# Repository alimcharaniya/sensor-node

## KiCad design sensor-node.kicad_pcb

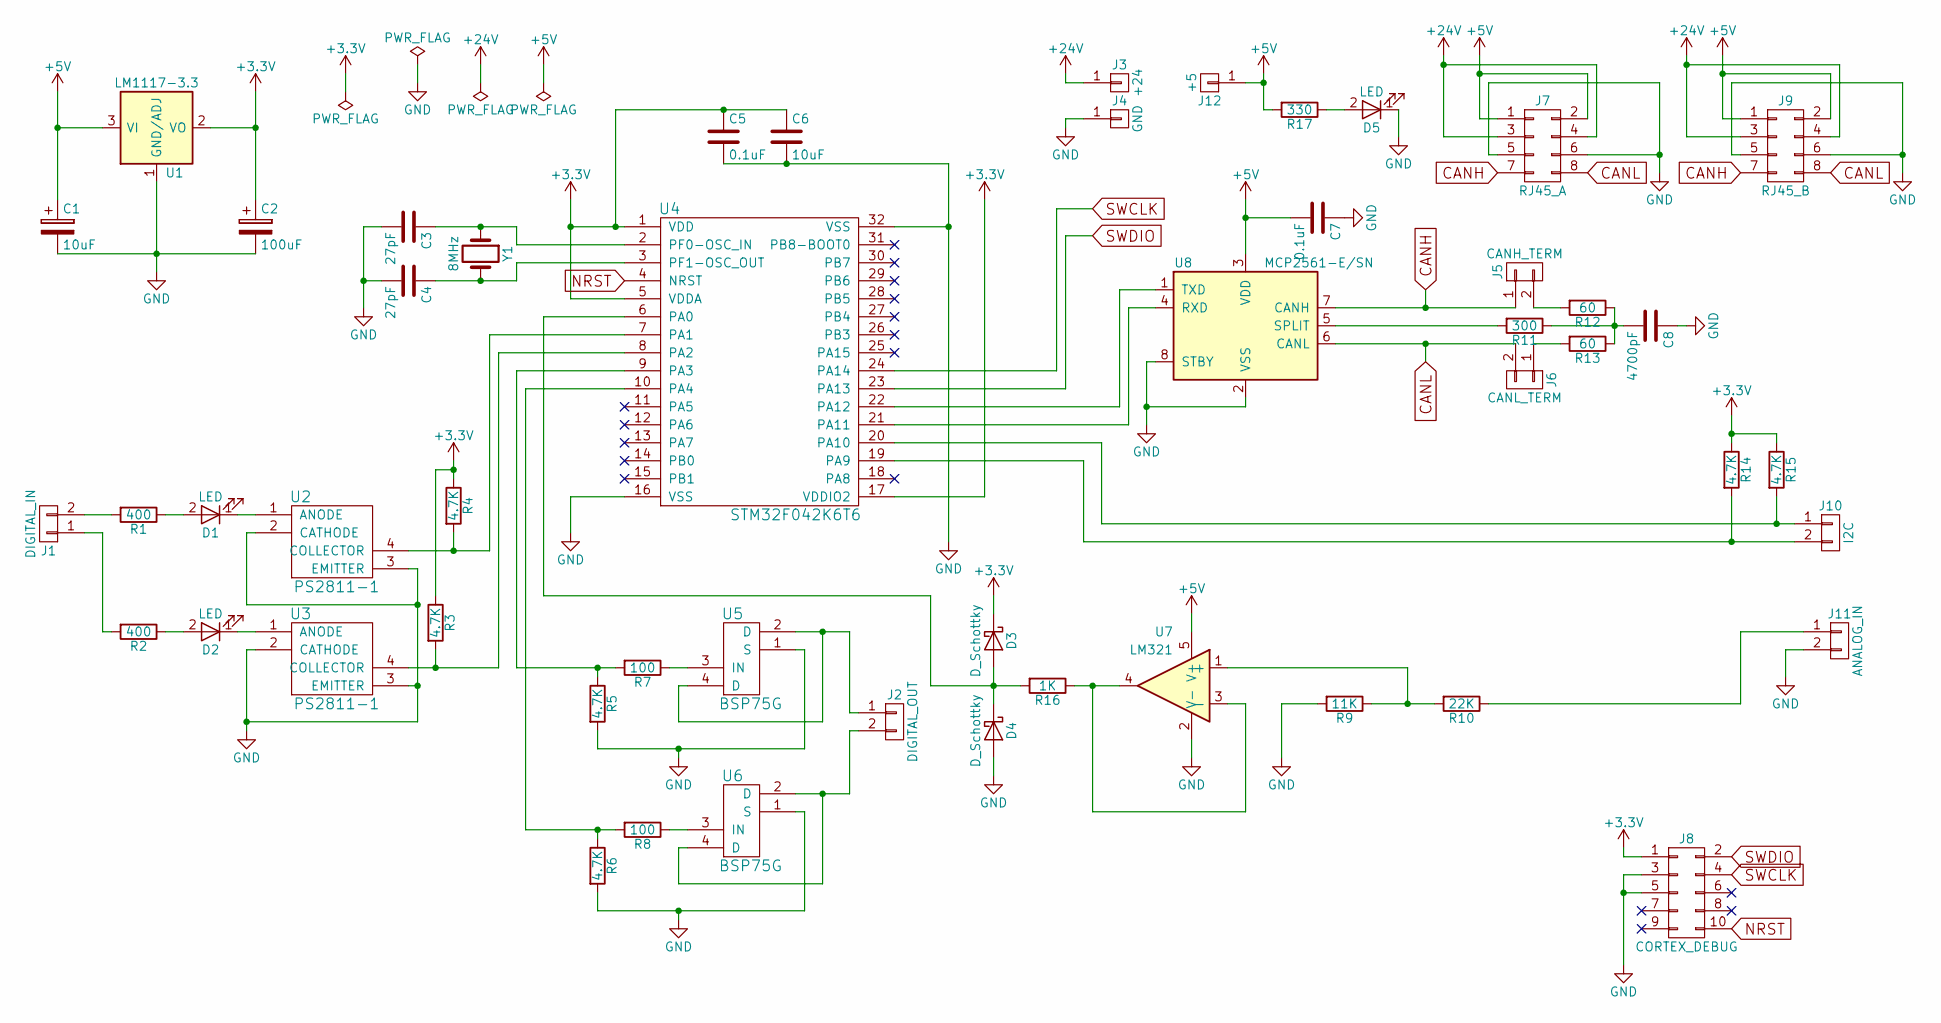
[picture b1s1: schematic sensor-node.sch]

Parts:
C1, C6: 10uF; C_0805_HandSoldering
C2: 100uF; C_1210_HandSoldering
C3, C4: 27pF; C_0805_HandSoldering
C5, C7: 0.1uF; C_0805_HandSoldering
C8: 4700pF; C_0805_HandSoldering
D1, D2, D5: LED; D_0805
D3, D4: D_Schottky; D_0805
J1: DIGITAL_IN; TerminalBlock_Pheonix_MKDS1.5-2pol
J2: DIGITAL_OUT; TerminalBlock_Pheonix_MKDS1.5-2pol
J3: +24; AB2_0.25_QD_TAB
J4: GND; AB2_0.25_QD_TAB
J5: CANH_TERM; Pin_Header_Straight_1x02_Pitch2.54mm
J6: CANL_TERM; Pin_Header_Straight_1x02_Pitch2.54mm
J7: RJ45_A; RJ45_8
J8: CORTEX_DEBUG; Pin_Header_Straight_2x05_Pitch1.27mm
J9: RJ45_B; RJ45_8
J10: I2C; TerminalBlock_Pheonix_MKDS1.5-2pol
J11: ANALOG_IN; TerminalBlock_Pheonix_MKDS1.5-2pol
J12: +5; AB2_0.25_QD_TAB
R1, R2: 400; R_0805_HandSoldering
R3, R4, R5, R6, R14, R15: 4.7K; R_0805_HandSoldering
R7, R8: 100; R_0805_HandSoldering
R9: 11K; R_0805_HandSoldering
R10: 22K; R_0805_HandSoldering
R11: 300; R_0805_HandSoldering
R12, R13: 60; R_0805_HandSoldering
R16: 1K; R_0805_HandSoldering
R17: 330; R_0805_HandSoldering
U1: LM1117-3.3; SOT-223
U2, U3: PS2811-1; SOP-4_4.4x2.8mm_Pitch1.27mm
U4: STM32F042K6T6; LQFP-32_7x7mm_Pitch0.8mm
U5, U6: BSP75G; SOT-223
U7: LM321; SOT-23-5
U8: MCP2561-E/SN; SOIC-8_3.9x4.9mm_Pitch1.27mm
Y1: 8MHz; Crystal_SMD_HC49-SD_HandSoldering

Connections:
+3V3: C2.1, C5.1, C6.1, D3.1 (K), J8.1, R3.1, R4.1, R14.1, R15.1, U1.2 (VO), U1.4 (VO), U4.1 (VDD), U4.5 (VDDA), U4.17 (VDDIO2)
+5V: C1.1, C7.2, J7.1, J7.2, J9.1, J9.2, J12.1, R17.2, U1.3 (VI), U7.5 (V+), U8.3 (VDD)
+24V: J3.1, J7.3, J7.4, J9.3, J9.4
CANH: J5.1, J7.7, J9.7, U8.7 (CANH)
CANL: J6.2, J7.8, J9.8, U8.6 (CANL)
GND: C1.2, C2.2, C3.2, C4.2, C5.2, C6.2, C7.1, C8.1, D4.2 (A), D5.1 (K), J4.1, J7.5, J7.6, J8.3, J8.5, J9.5, J9.6, J11.2, R5.2, R6.2, R9.2, U1.1 (GND/ADJ), U2.2 (CATHODE), U2.3 (EMITTER), U3.2 (CATHODE), U3.3 (EMITTER), U4.16 (VSS), U4.32 (VSS), U5.1 (S), U6.1 (S), U7.2 (V-), U8.2 (VSS), U8.8 (STBY)
NRST: J8.10, U4.4 (NRST)
unnamed: C3.1, U4.2 (PF0-OSC_IN), Y1.1
unnamed: C4.1, U4.3 (PF1-OSC_OUT), Y1.2
unnamed: C8.2, R11.1, R12.1, R13.1
unnamed: D1.1 (K), U2.1 (ANODE)
unnamed: D1.2 (A), R1.1
unnamed: D2.1 (K), U3.1 (ANODE)
unnamed: D2.2 (A), R2.1
unnamed: D3.2 (A), D4.1 (K), R16.2, U4.6 (PA0)
unnamed: D5.2 (A), R17.1
unnamed: J1.1, R2.2
unnamed: J1.2, R1.2
unnamed: J2.1, U5.2 (D), U5.4 (D)
unnamed: J2.2, U6.2 (D), U6.4 (D)
unnamed: J5.2, R12.2
unnamed: J6.1, R13.2
unnamed: J10.1, R15.2, U4.20 (PA10)
unnamed: J10.2, R14.2, U4.19 (PA9)
unnamed: J11.1, R10.1
unnamed: R3.2, U3.4 (COLLECTOR), U4.8 (PA2)
unnamed: R4.2, U2.4 (COLLECTOR), U4.7 (PA1)
unnamed: R5.1, R7.2, U4.9 (PA3)
unnamed: R6.1, R8.2, U4.10 (PA4)
unnamed: R7.1, U5.3 (IN)
unnamed: R8.1, U6.3 (IN)
unnamed: R9.1, R10.2, U7.1 (+)
unnamed: R11.2, U8.5 (SPLIT)
unnamed: R16.1, U7.3 (-), U7.4
unnamed: U4.21 (PA11), U8.4 (RXD)
unnamed: U4.22 (PA12), U8.1 (TXD)
SWCLK: J8.4, U4.24 (PA14)
SWDIO: J8.2, U4.23 (PA13)

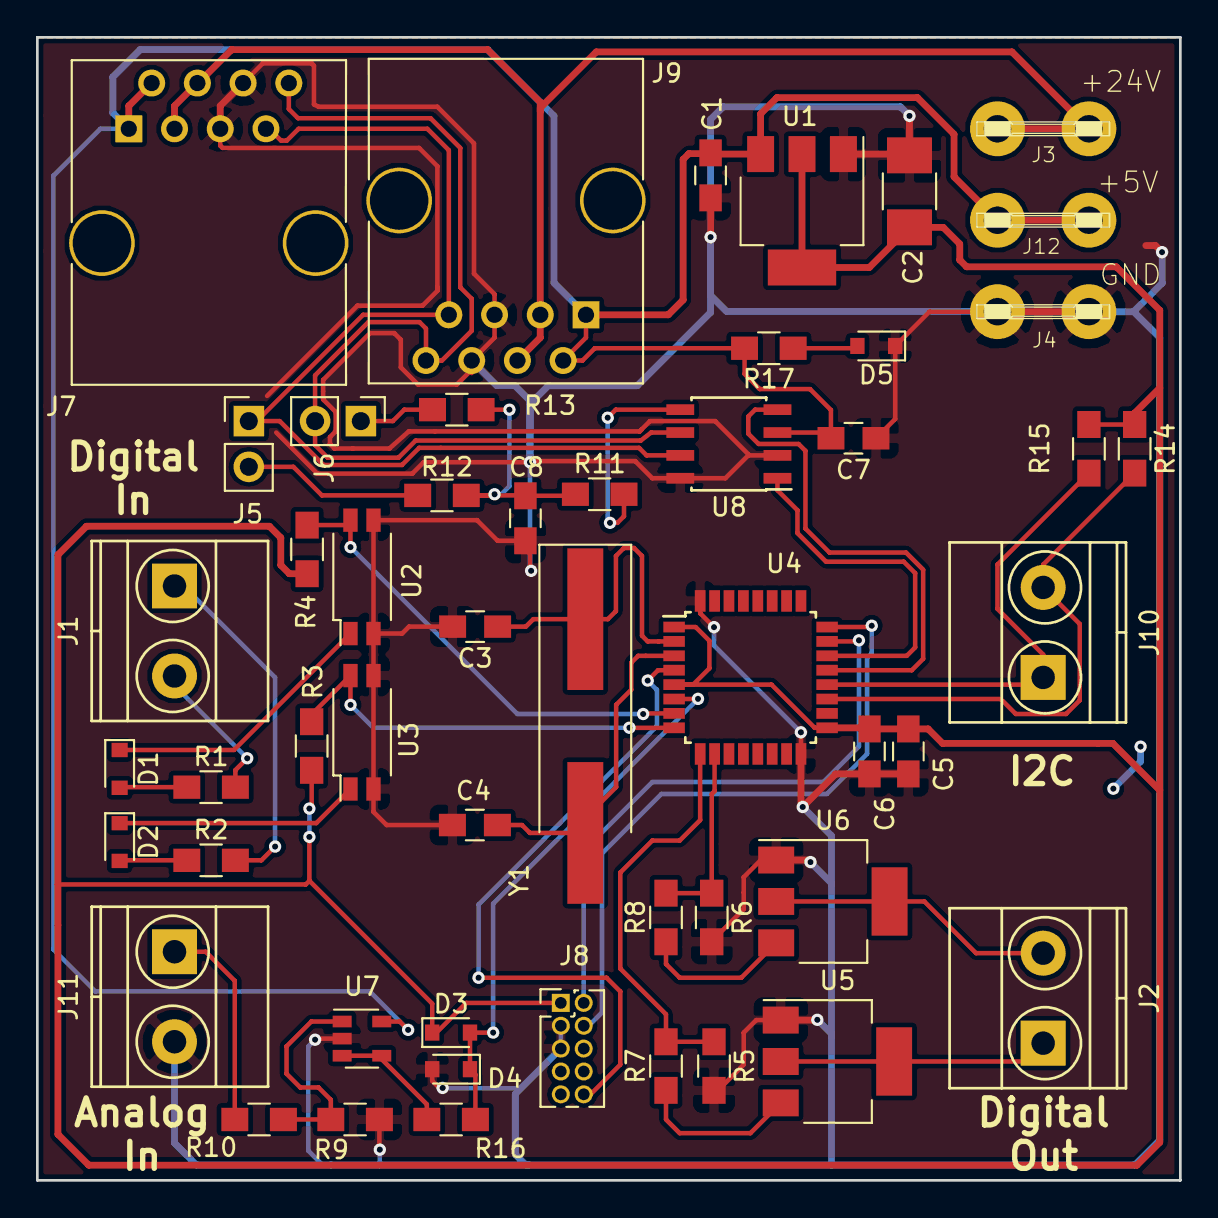
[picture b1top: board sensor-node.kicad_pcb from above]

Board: 2 copper layers, 63.5 x 63.5 mm, 51 parts (0 on the bottom side), 38 nets.

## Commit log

2017-07-20 init
2017-07-29 Layout chaged for better routing on the CAN differential
2017-07-31 Adding voltage divider/unity gain analog front end
2017-08-01 Final Version
2017-08-01 Osh Park Ready
2017-08-01 Osh Park label Done
